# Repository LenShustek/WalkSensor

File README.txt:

Battery-powered walk path sensor
 for clinical trials of therapies for movement disorders

  This is a small battery-powered wireless sensor that, when used
  in a pair on opposite sides of a walking path, detects someone
  walking through an IR beam between the sensors. It then sends a
  Bluetooth alert with detailed timing to a mobile phone or tablet.

  The custom-built sensor hardware consist of:
  - an AVR microprocessor
  - a Bluetooth LE radio module
  - 940nm IR LED transmitter powered by a constant-current driver
  - 940nm 38 Khz tuned IR receiver
  - red/green battery status light
  - blue and yellow operational status lights
  - power on/off pushbutton
  - program-controlled power supply circuit
  - enclosure with battery holder

Version 2 in 2017 used the Adafruit Bluefruit Feather 32U4 with an 
integrated Bluetooth module. The board used mostly through-hole 
components, and required tricky alignment of the LEDs into holes in the 
case. It was powered by 4 AA batteries in a rather clunky-looking square 
enclosure. 

Version 3 in 2020 uses a "raw" ATMega328P processor and a Microchip 
RN4870 Bluetooth module. All components are now surface mounted, 
including the LEDs which sit below light pipes in the cover. It is 
powered by a 9V battery in a sleeker case that looks more like a 
remote control.

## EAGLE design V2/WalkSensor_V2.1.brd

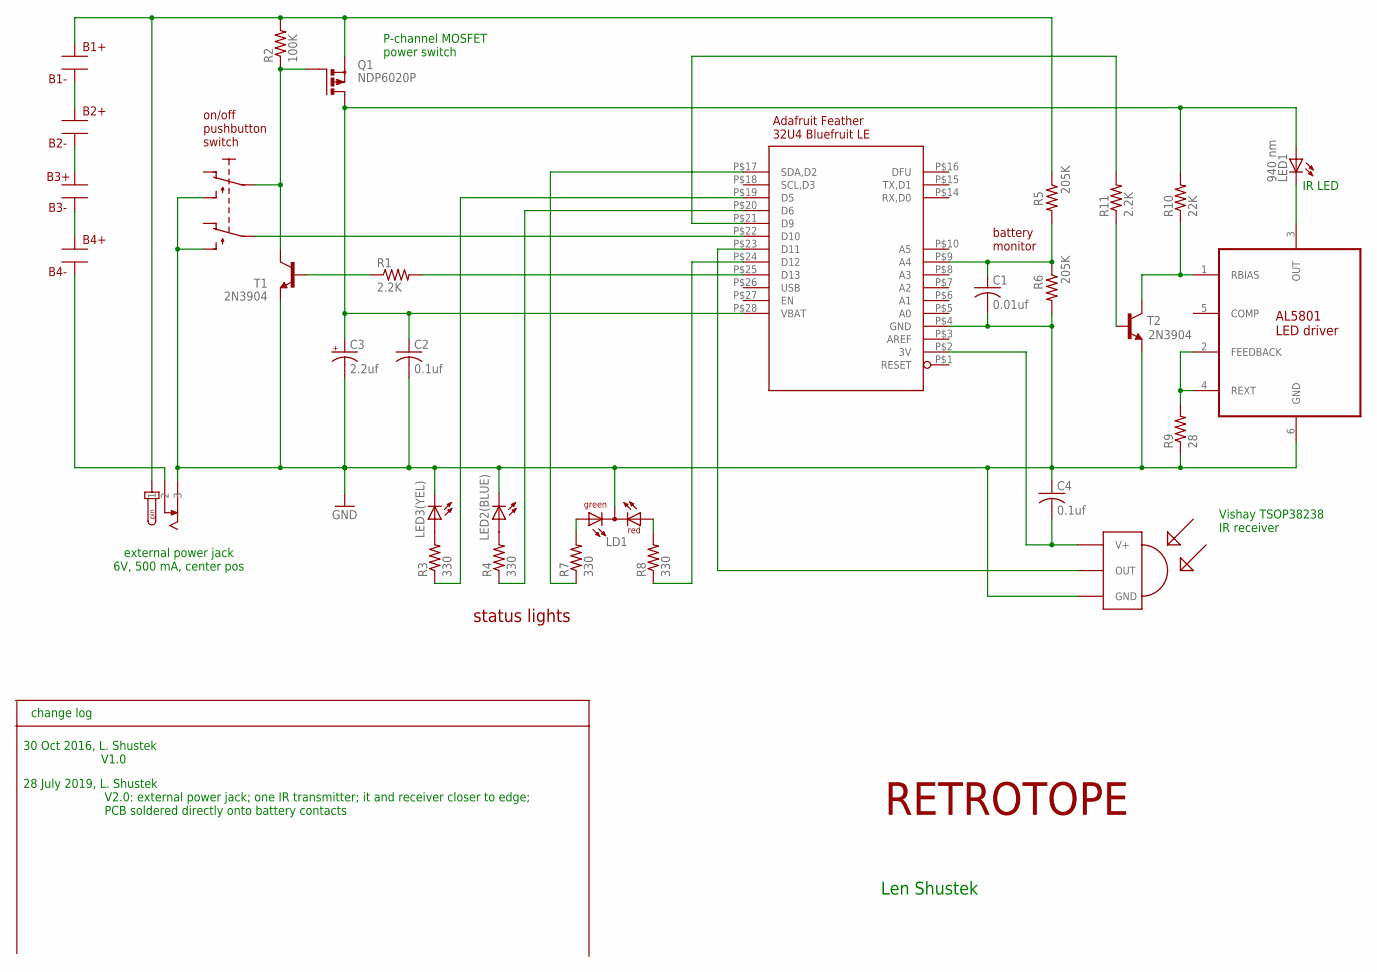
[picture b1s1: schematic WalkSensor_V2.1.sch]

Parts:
B1+, B1-, B2+, B2-, B3+, B3-, B4+, B4-: BATTERY_CONTACT
C1: 0.01uf; C025-025X050
C2, C4: 0.1uf; C025-025X050
C3: 2.2uf; E5-6
J1: DC_POWER_JACK
LD1: red/green; DUOLED-C-5MM
LED1: 940 nm; LED3MM
LED2(BLUE): blue; LED5MM
LED3(YEL): yellow; LED5MM
Q1: NDP6020P; TO220BH
R1, R11: 2.2K; 0207/10
R2: 100K; 0207/10
R3, R4, R7, R8: 330; 0207/10
R5, R6: 205K; 0207/10
R9: 28; 0207/10
R10: 22K; 0207/10
T1, T2: 2N3904; TO92-EBC
U1: AL5801; SOT95P280X130-6N
U$2: PUSHBUTTON-DPDT
U$3: TSOP1830; TSOP18XX
U$4: BLUEFRUIT-LE

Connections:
3V: C4.2, U$3.VCC (V+), U$4.P$2 (3V)
GND: C1.2, C2.2, C3.-, C4.1, J1.P$5 (3), LD1.C, LED2(BLUE).K (C), LED3(YEL).K (C), R6.2, R9.1, T1.E, T2.E, U1.6 (GND), U$2.P$1 (S), U$2.P$2 (S1), U$3.GND, U$4.P$4 (GND)
unnamed: U$2.P$6 (P1), U$4.P$22 (D10)
unnamed: LED3(YEL).A, R3.2
unnamed: B1+.P$1, J1.P$1 (1), Q1.S, R2.2, R5.1
unnamed: LED2(BLUE).A, R4.2
unnamed: Q1.G, R2.1, T1.C, U$2.P$5
unnamed: R11.1, T2.B
unnamed: R1.2, U$4.P$25 (D13)
unnamed: R1.1, T1.B
unnamed: R4.1, U$4.P$20 (D6)
unnamed: R3.1, U$4.P$19 (D5)
unnamed: LED1.K (C), U1.3 (OUT)
unnamed: R11.2, U$4.P$21 (D9)
unnamed: LD1.AG, R7.2
unnamed: LD1.AR, R8.2
unnamed: B1-.P$1, B2+.P$1
unnamed: R7.1, U$4.P$17 (SDA,D2)
unnamed: B2-.P$1, B3+.P$1
unnamed: U$3.OUT, U$4.P$23 (D11)
unnamed: R9.2, U1.2 (FEEDBACK), U1.4 (REXT)
unnamed: C1.1, R5.2, R6.1, U$4.P$9 (A4)
unnamed: R10.1, T2.C, U1.1 (RBIAS)
unnamed: R8.1, U$4.P$24 (D12)
unnamed: B3-.P$1, B4+.P$1
unnamed: B4-.P$1, J1.P$3 (2)
VBAT: C2.1, C3.+, LED1.A, Q1.D, R10.2, U$4.P$28 (VBAT)

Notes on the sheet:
Vishay TSOP38238 IR receiver
IR LED
P-channel MOSFET power switch
change log
30 Oct 2016, L. Shustek V1.0
Len Shustek
RETROTOPE
status lights
on/off pushbutton switch
battery monitor
Adafruit Feather 32U4 Bluefruit LE
external power jack 6V, 500 mA, center pos
28 July 2019, L. Shustek V2.0: external power jack; one IR transmitter; it and receiver closer to edge; PCB soldered directly onto battery contacts

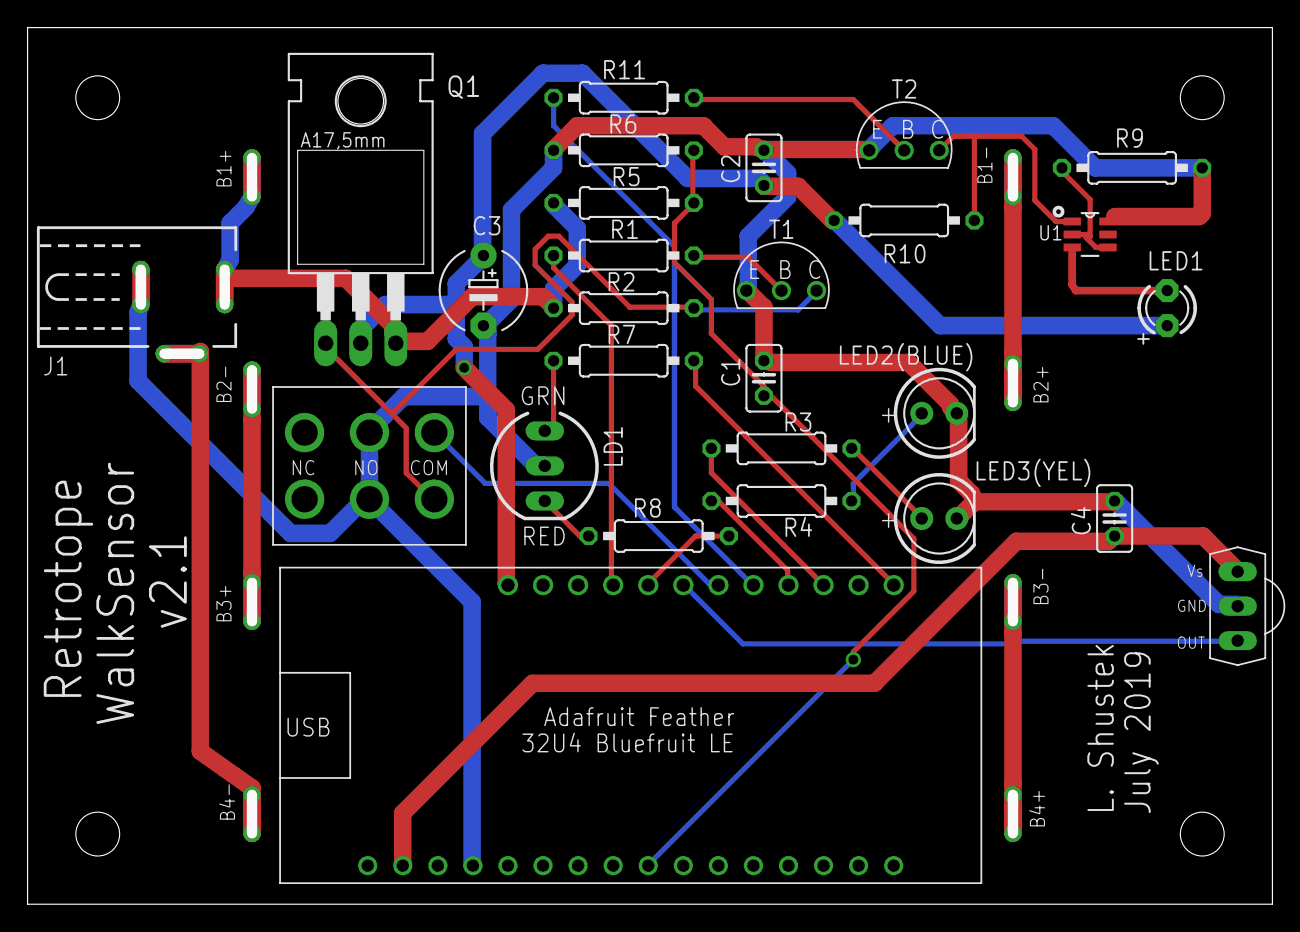
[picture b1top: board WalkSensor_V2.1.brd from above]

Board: 2 copper layers, 89.4 x 62.7 mm, 35 parts (0 on the bottom side), 27 nets.

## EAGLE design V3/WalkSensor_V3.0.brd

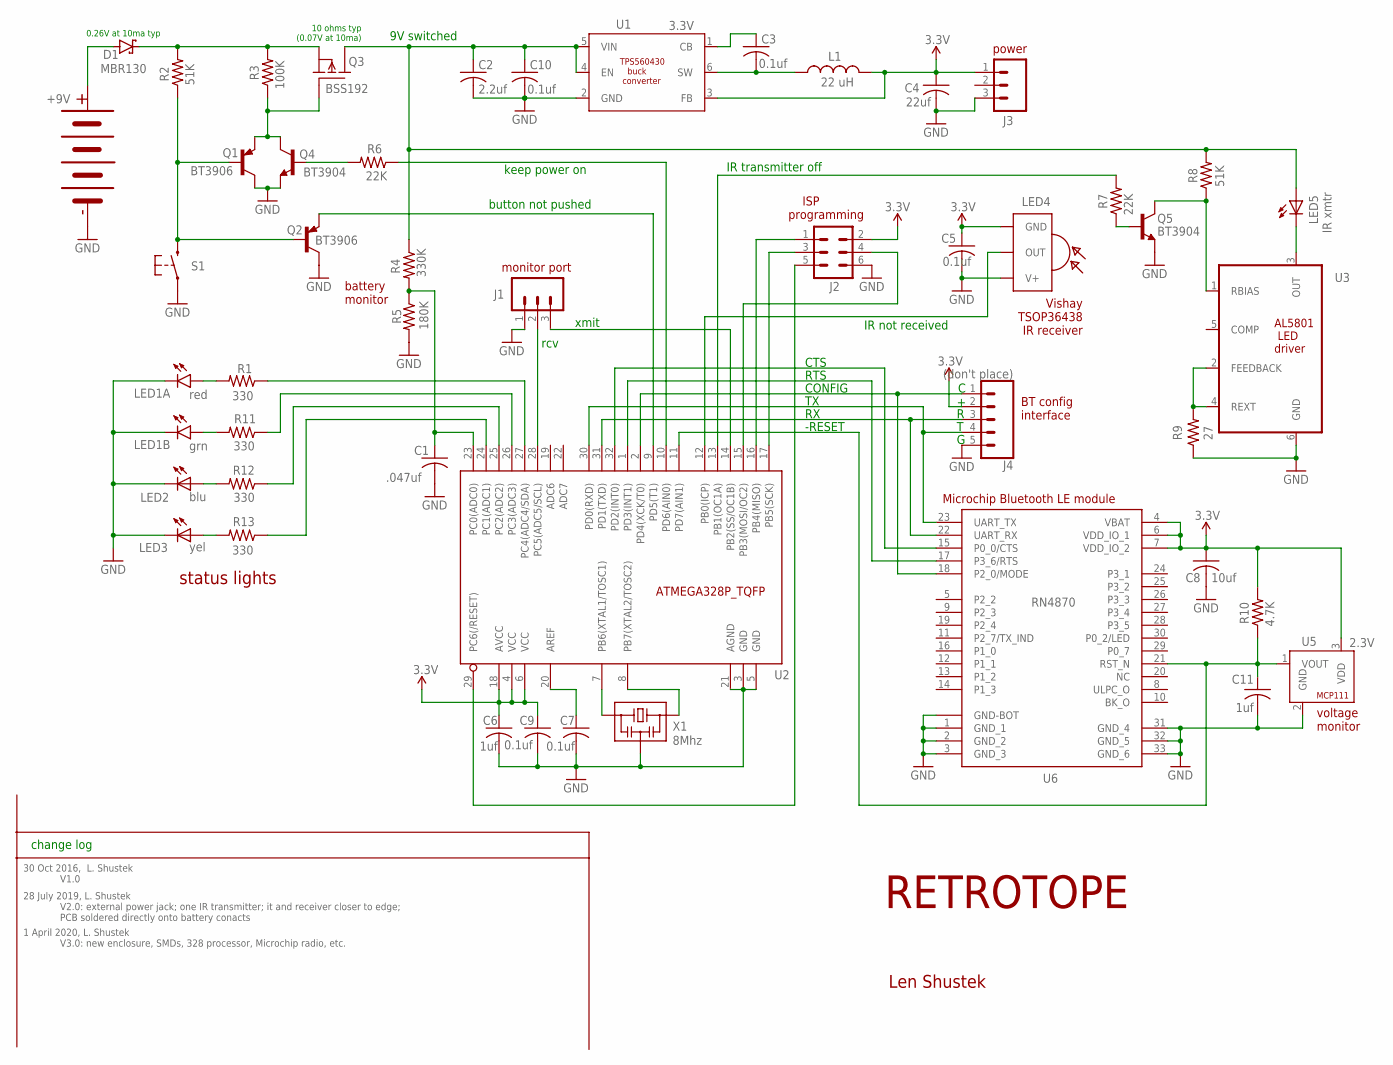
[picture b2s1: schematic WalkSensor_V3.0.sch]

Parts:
B1: 9V battery wires; 4-CELL-BATTERY
C1: .047uf; C0805
C2: 2.2uf; C1210
C3, C5, C7, C9, C10: 0.1uf; C0805
C4: 22uf; C1210
C6, C11: 1uf; C0805
C8: 10uf; C1210
D1: MBR130; SOD123-2
J1, J3: (don't place); 1X03
J2: ISP pgm connector; 2X3_SMT
J4: (don't place); 1X05
L1: 22 uH; L1812
LED1: red/grn; P-LCC4-1
LED2: blu; LED_PLCC-2
LED3: yel; LED_PLCC-2
LED4: IR rcvr; VISHAY_TSOP_SMD_SIDE
LED5: IR xmtr; LED_VISHAY_VSMB2948
Q1, Q2: BT3906; SOT23-3
Q3: BSS192; SOT89
Q4, Q5: BT3904; SOT23-3
R1, R11, R12, R13: 330; M0805
R2, R8: 51K; M0805
R3: 100K; M0805
R4: 330K; M0805
R5: 180K; M0805
R6, R7: 22K; M0805
R9: 27; M0805
R10: 4.7K; M0805
S1: pushbutton; SWITCH_C&K_GULLWING
U1: 3.3V; SOT23-6
U2: ATMEGA328P_TQFP; TQFP32-08
U3: AL5801; SOT95P280X130-6N
U5: 2.3V; SC70-3-R
U6: RN4870
X1: 8Mhz; CSTNE

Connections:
3.3V: C4.1, C5.1, C6.1, C8.1, C9.1, J2.2, J3.1, J4.2, L1.2, LED4.P$1 (GND), R10.2, U1.3 (FB), U2.4 (VCC), U2.6 (VCC), U2.18 (AVCC), U5.3 (VDD), U6.4 (VBAT), U6.6 (VDD_IO_1), U6.7 (VDD_IO_2)
GND: B1.P$1, C1.2, C2.2, C4.2, C5.2, C6.2, C7.2, C8.2, C9.2, C10.2, C11.2, J1.1, J2.6, J3.3, J4.5, LED1.P$1 (C), LED1.P$4 (C), LED2.P$2 (C), LED3.P$2 (C), LED4.P$3 (V+), Q1.3 (C), Q2.3 (C), Q4.2 (E), Q5.2 (E), R5.2, R9.1, S1.P$1 (1), S1.P$2 (1), U1.2 (GND), U2.3 (GND), U2.5 (GND), U2.21 (AGND), U3.6 (GND), U5.2 (GND), U6.1 (GND_1), U6.2 (GND_2), U6.3 (GND_3), U6.31 (GND_4), U6.32 (GND_5), U6.33 (GND_6), U6.GND (GND-BOT), X1.P$2 (2)
unnamed: C3.1, U1.1 (CB)
unnamed: LED1.P$2 (A), R1.2
unnamed: U2.8 (PB7(XTAL2/TOSC2)), X1.P$3 (3)
unnamed: LED1.P$3 (A), R11.2
unnamed: U2.7 (PB6(XTAL1/TOSC1)), X1.P$1 (1)
unnamed: Q5.1 (B), R7.1
unnamed: D1.P$2 (C), Q3.3 (S), R2.2, R3.2
unnamed: C3.2, L1.1, U1.6 (SW)
unnamed: R1.1, U2.27 (PC4(ADC4/SDA))
unnamed: R11.1, U2.26 (PC3(ADC3))
unnamed: LED5.P$1 (C), U3.3 (OUT)
unnamed: R7.2, U2.13 (PB1(OC1A))
unnamed: LED2.P$1 (A), R12.2
unnamed: LED3.P$1 (A), R13.2
unnamed: J4.3, U2.31 (PD1(TXD)), U6.22 (UART_RX)
unnamed: R12.1, U2.25 (PC2(ADC2))
unnamed: Q1.2 (E), Q3.1 (G), Q4.3 (C), R3.1
unnamed: Q4.1 (B), R6.2
unnamed: R9.2, U3.2 (FEEDBACK), U3.4 (REXT)
unnamed: C1.1, R4.2, R5.1, U2.23 (PC0(ADC0))
unnamed: Q5.3 (C), R8.1, U3.1 (RBIAS)
unnamed: R13.1, U2.24 (PC1(ADC1))
unnamed: Q2.2 (E), U2.9 (PD5(T1))
unnamed: J2.1, U2.16 (PB4(MISO))
unnamed: LED4.P$4 (OUT), U2.12 (PB0(ICP))
unnamed: J2.3, U2.17 (PB5(SCK))
unnamed: J4.4, U2.30 (PD0(RXD)), U6.23 (UART_TX)
unnamed: J1.2, U2.28 (PC5(ADC5/SCL))
unnamed: R6.1, U2.10 (PD6(AIN0))
unnamed: J2.5, U2.29 (PC6(/RESET))
unnamed: J4.1, U2.2 (PD4(XCK/T0)), U6.18 (P2_0/MODE)
unnamed: Q1.1 (B), Q2.1 (B), R2.1, S1.P$3 (3), S1.P$4 (3)
unnamed: J1.3, U2.14 (PB2(SS/OC1B))
unnamed: U2.32 (PD2(INT0)), U6.15 (P0_0/CTS)
unnamed: C7.1, U2.20 (AREF)
unnamed: J2.4, U2.15 (PB3(MOSI/OC2))
unnamed: U2.1 (PD3(INT1)), U6.17 (P3_6/RTS)
unnamed: C11.1, R10.1, U2.11 (PD7(AIN1)), U5.1 (VOUT), U6.21 (RST_N)
unnamed: C2.1, C10.1, LED5.P$2 (A), Q3.2 (D), Q3.2@1 (D), R4.1, R8.2, U1.4 (EN), U1.5 (VIN)
unnamed: B1.P$2, D1.P$1 (A)

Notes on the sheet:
Vishay TSOP36438 IR receiver
change log
30 Oct 2016, L. Shustek V1.0
Len Shustek
RETROTOPE
status lights
battery monitor
28 July 2019, L. Shustek V2.0: external power jack; one IR transmitter; it and receiver closer to edge; PCB soldered directly onto battery conacts
1 April 2020, L. Shustek V3.0: new enclosure, SMDs, 328 processor, Microchip radio, etc.
+9V
ISP programming
monitor port
keep power on
button not pushed
power
BT config interface
CTS
RTS
CONFIG
-RESET
voltage monitor
red
rcv
xmit
0.26V at 10ma typ
10 ohms typ (0.07V at 10ma)
9V switched
IR transmitter off
IR not received
grn
Microchip Bluetooth LE module

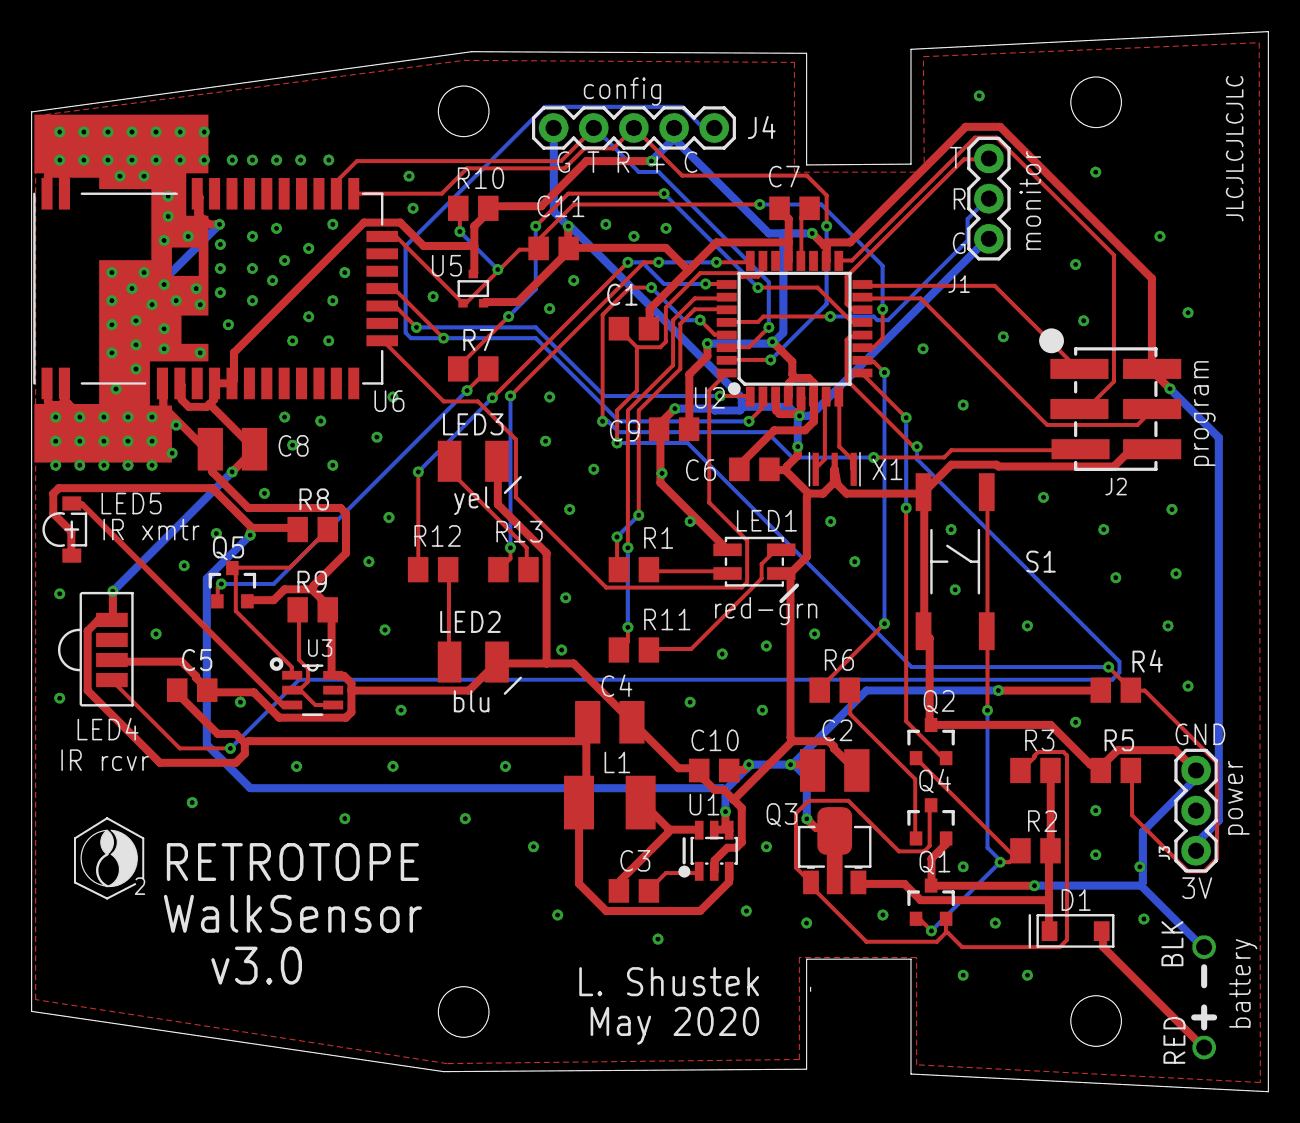
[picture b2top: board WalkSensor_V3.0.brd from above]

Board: 2 copper layers, 78.2 x 67.1 mm, 48 parts (0 on the bottom side), 42 nets.

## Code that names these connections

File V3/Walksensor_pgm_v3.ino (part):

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
/* The multiple schemes for pin numbering is confusing!
   IDE  port  TQFP pin  use
   A0  PC0      23     battery monitor
   A1  PC1      24     yellow LED
   A2  PC2      25     blue LED
   A3  PC3      26     green LED
   A4  PC4      27     red LED
   A5  PC5      28     debug serial receive (must be PC, or PD, not PB)
   --  ADC6     19     (unusable for digital I/O)
   --  ADC7     22     (unusable for digital I/O)
   0   PD0      30     RxD from Bluetooth module
   1   PD1      31     TxD to Bluetooth module
   2   PD2      32     RTS from Bluetooth module  (unused presently)
   3   PD3      1      CTS from Bluetooth module  (unused presently)
   4   PD4      2      Config to Bluetooth module (unused presently)
   5   PD5      9      "button not pushed" input (also OC0B)
   6   PD6      10     "keep power on" output (also OC0A)
   7   PD7      11     - RESET to Bluetooth module
   8   PB0      12     IR receiver input (causes PB0 pin change interrupt)
   9   PB1      13     IR LED transmit (output of Counter / Timer 1)
   10  PB2      14     debug serial transmit
   11  PB3      15     ISP MOSI
   12  PB4      16     ISP MISO
   13  PB5      17     ISP SCK
   --  PC6      29     ISP CPU reset  */

#define POWERUP_FET 6       // output pin high keeps us powered up by turning the MOSFET on
#define POWERDOWN_SW 5      // this input pin (needs internal pullup) is low if the on/off button is pushed
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#define LED_RED A4

#define IR_TRANSMIT 9      // active low output pin for IR transmit through constant-current LED driver
//.                           This is PB1, but more importantly, the OC1A output for Timer/Counter1.
#define IR_RECEIVE 8       // active low input pin if IR receiver sees 10 or more pulses at 38 Khz
//.                           This must be on port B, C, or D to allow pin-change interrupts.

// Microchip RN4870 Bluetooth LE module pin assignments
#define BT_RX 0            // receive data from BT (its transmit)
#define BT_TX 1            // PD1: xmit data to BT (its receive)
#define BT_TX_PORT PORTD          // data port D using normal address for load/store
#define BT_TX_MASK 0x02           // mask for bit 1
#define BT_RESET 7         // active low reset 
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#define DEBUG_TX 10        // software serial transmit line

#if MARKLOCATION && !DEBUG          // pin for scope or logic analyzer tracing
   #define LOCATION_MARKER_PIN 10      // PB2, and CAN'T BE USED WITH DEBUG ON!
   #define LOCATION_MARKER_PORT 0x05   // data port B using the 0-based address for SBI/CBI instructions
   #define LOCATION_MARKER_BIT 2       // bit number (not mask) of the scope pin
#endif
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
// In order to compile the interrupt routine with DEBUG on, we use a local version of
// SoftwareSerial that only takes over the interrupt vector for the pin-change interrupt
// on the receive pin it actually uses, which is PC5, interrupt PCINT1. That way we
// get to take over PCINT0 for the IR receiver's pin change interrupt.

static unsigned long pulse_start_time;
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   else
      flashlights(100, 3); // 200 msec flash, 3 times

   // to save power, turn off digital inputs on PD6/7 (Arduiino pins 6/7, TQFP pins 10/11)
   DIDR1 = (1 << AIN1D) | (1 << AIN0D);
   // similarly for PC0-4 (A0-A4), and for PC5 (A5) if it is not used as input for the debug port
   DIDR0 = (1 << ADC4D) | (1 << ADC3D) | (1 << ADC2D) | (1 << ADC1D) | (1 << ADC0D)
           | (DEBUG ? 0 : (1 << ADC5D));

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
   // see if we are receiving the beam from the other unit, and configure accordingly
   falling_pulses = short_pulses = 0;
   PCICR  |= 0x01;      // enable pin-change interrupts PCINT0 for PCINT[7:0], PB7:0
   PCMSK0 = 0x01;       // enable only on PB0, Arduino pin 8 (PCINT0, TQFP-32 package pin 12)
   delay(CHK_RCV_TIME); // wait to see if we receive IR pulses
   #if DEBUG
   debug_serial.print("rcvd:"); debug_serial.print(falling_pulses);
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
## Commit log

2016-11-08 preliminary beta release
2016-11-11 beta v2
2016-11-21 closer to production
2016-11-22 closer to production
2019-10-12 update to version 2
2020-05-17 Added V2 to reorganized repository

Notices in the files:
V3/Walksensor_pgm_v3.ino:
Copyright (c) 2016,2020 Len Shustek
The MIT License (MIT)
parts and their libraries:
SparkFun-IC-Microcontroller: Licensing: Creative Commons ShareAlike 4.0 International - https://creativecommons.org/licenses/by-sa/4.0
